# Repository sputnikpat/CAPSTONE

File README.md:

# CAPSTONE
This is the college capstone project.

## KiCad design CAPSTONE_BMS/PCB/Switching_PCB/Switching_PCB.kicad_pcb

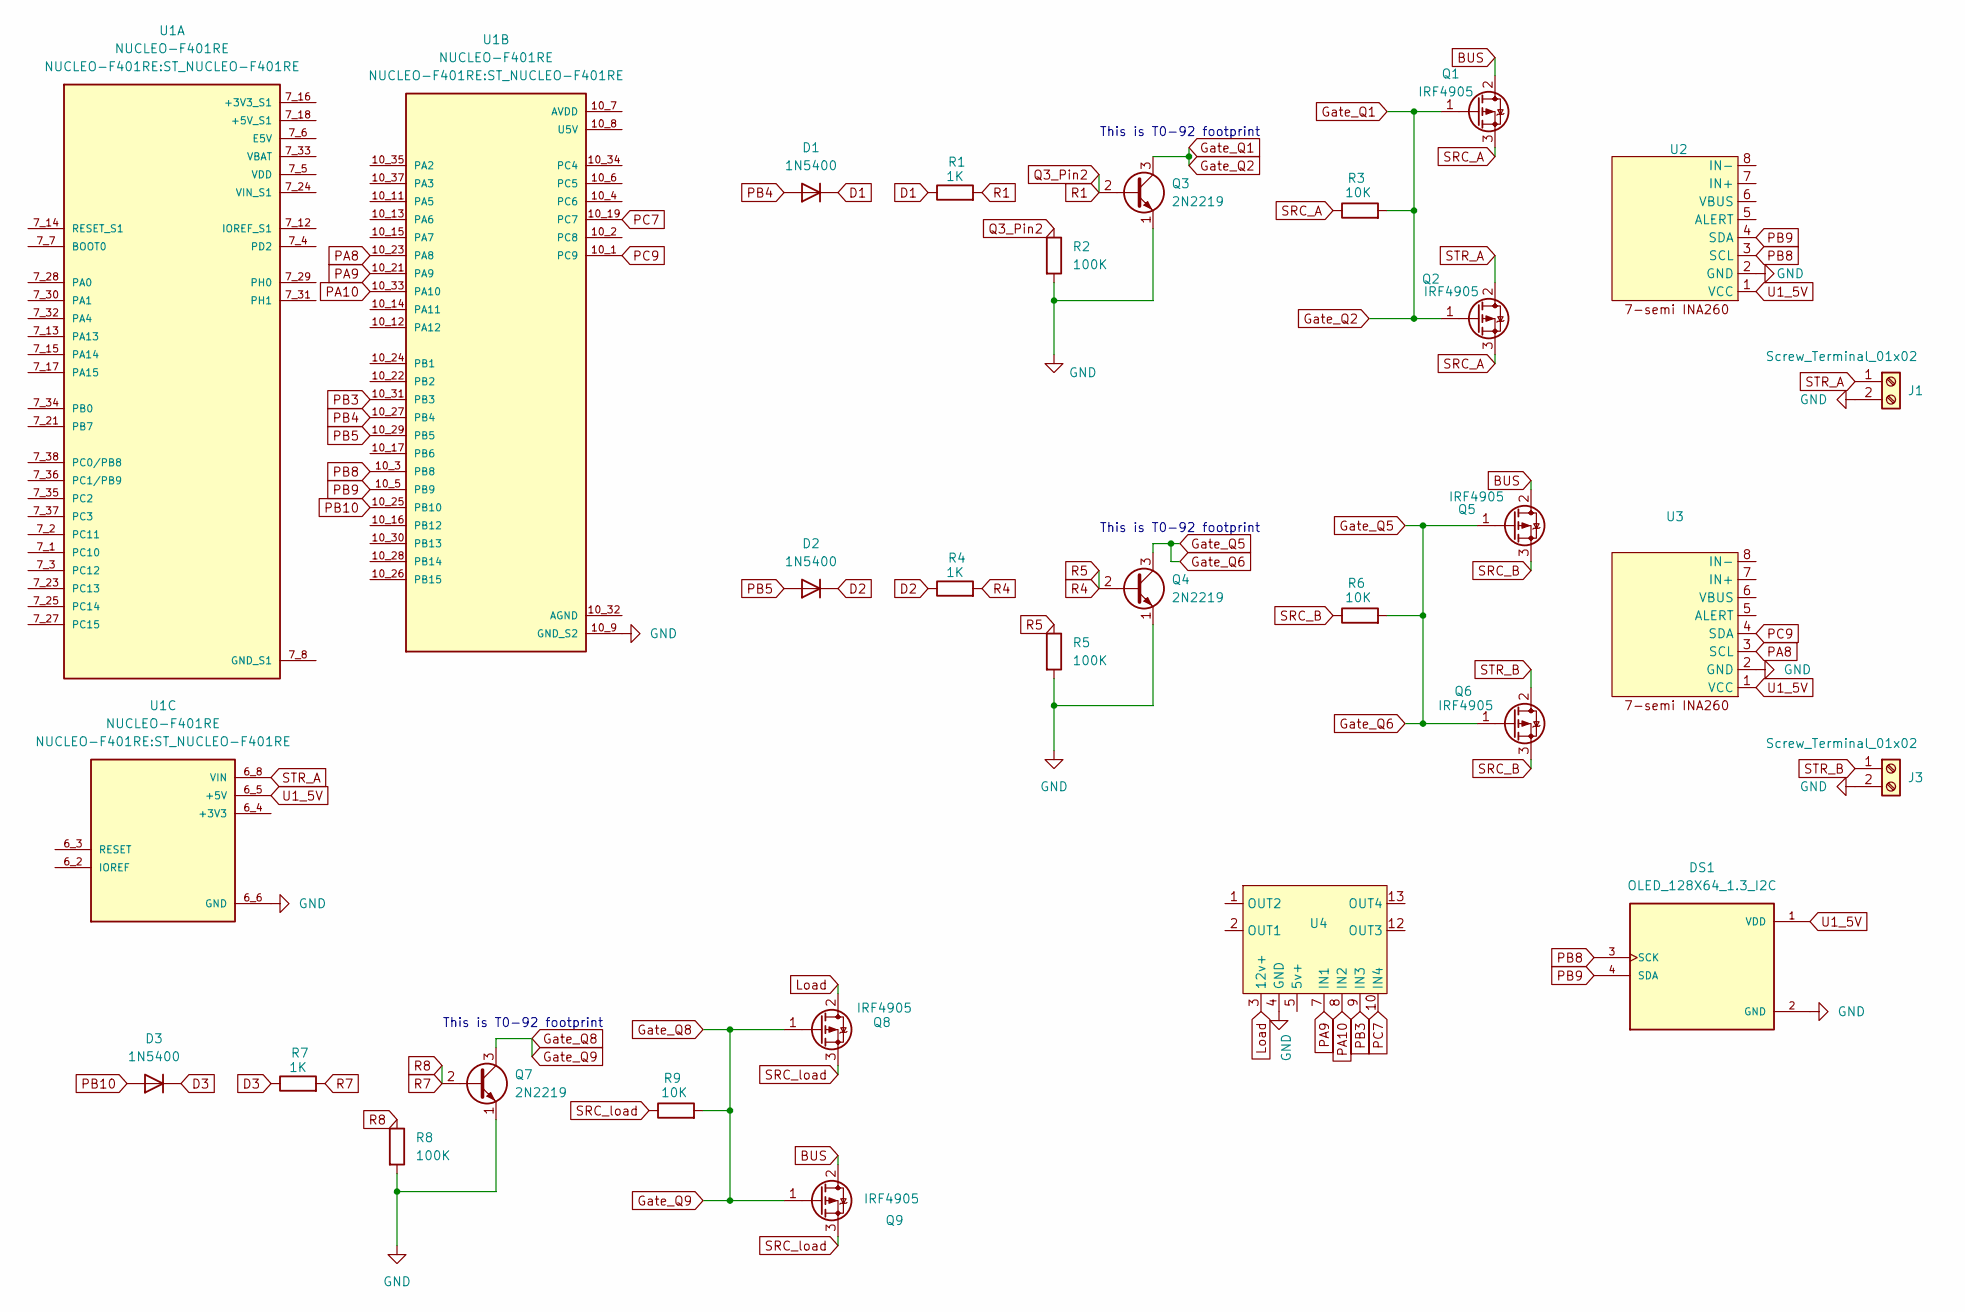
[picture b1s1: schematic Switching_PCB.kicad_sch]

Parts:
D1, D2, D3: 1N5400; D_DO-201AD_P15.24mm_Horizontal
DS1: OLED_128X64_1.3_I2C; LCD_OLED_128X64_1.3_I2C; PARTREV NA
J1, J3: Screw_Terminal_01x02; TerminalBlock_MaiXu_MX126-5.0-02P_1x02_P5.00mm
Q1, Q2, Q5, Q6, Q8, Q9: IRF4905; TO-220-3_Vertical
Q3, Q4, Q7: 2N2219; TO-92
R1, R4, R7: 1K; R_Axial_DIN0204_L3.6mm_D1.6mm_P5.08mm_Horizontal
R2, R5, R8: 100K; R_Axial_DIN0204_L3.6mm_D1.6mm_P5.08mm_Horizontal
R3, R6, R9: 10K; R_Axial_DIN0204_L3.6mm_D1.6mm_P5.08mm_Horizontal
U1: NUCLEO-F401RE; ST_NUCLEO-F401RE; PARTREV 13
U2, U3: INA260_board
U4: L298_MotorDriver

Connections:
BUS: Q1.2 (D), Q5.2 (D), Q9.2 (D)
D1: D1.1 (K), R1.1
D2: D2.1 (K), R4.1
D3: D3.1 (K), R7.1
GND: DS1.2 (GND), J1.2, J3.2, Q3.1 (E), Q4.1 (E), Q7.1 (E), R2.2, R5.2, R8.2, U1.6_6 (GND), U1.6_7 (GND), U1.10_9 (GND_S2), U1.10_20 (GND_S2), U2.2 (GND), U3.2 (GND), U4.4 (GND)
GND_S1: U1.7_8 (GND_S1), U1.7_19 (GND_S1), U1.7_20 (GND_S1), U1.7_22 (GND_S1)
Gate_Q1: Q1.1 (G), Q2.1 (G), Q3.3 (C), R3.2
Gate_Q5: Q4.3 (C), Q5.1 (G), Q6.1 (G), R6.2
Gate_Q8: Q7.3 (C), Q8.1 (G), Q9.1 (G), R9.2
Load: Q8.2 (D), U4.3 (12v+)
PA8: U1.10_23 (PA8), U3.3 (SCL)
PA9: U1.10_21 (PA9), U4.7 (IN1)
PA10: U1.10_33 (PA10), U4.8 (IN2)
PB3: U1.10_31 (PB3), U4.9 (IN3)
PB4: D1.2 (A), U1.10_27 (PB4)
PB5: D2.2 (A), U1.10_29 (PB5)
PB8: DS1.3 (SCK), U1.10_3 (PB8), U2.3 (SCL)
PB9: DS1.4 (SDA), U1.10_5 (PB9), U2.4 (SDA)
PB10: D3.2 (A), U1.10_25 (PB10)
PC7: U1.10_19 (PC7), U4.10 (IN4)
PC9: U1.10_1 (PC9), U3.4 (SDA)
Q3_Pin2: Q3.2 (B), R1.2, R2.1
R4: Q4.2 (B), R4.2, R5.1
R7: Q7.2 (B), R7.2, R8.1
SRC_A: Q1.3 (S), Q2.3 (S), R3.1
SRC_B: Q5.3 (S), Q6.3 (S), R6.1
SRC_load: Q8.3 (S), Q9.3 (S), R9.1
STR_A: J1.1, Q2.2 (D), U1.6_8 (VIN)
STR_B: J3.1, Q6.2 (D)
U1_5V: DS1.1 (VDD), U1.6_5 (+5V), U2.1 (VCC), U3.1 (VCC)

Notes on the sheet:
This is T0-92 footprint

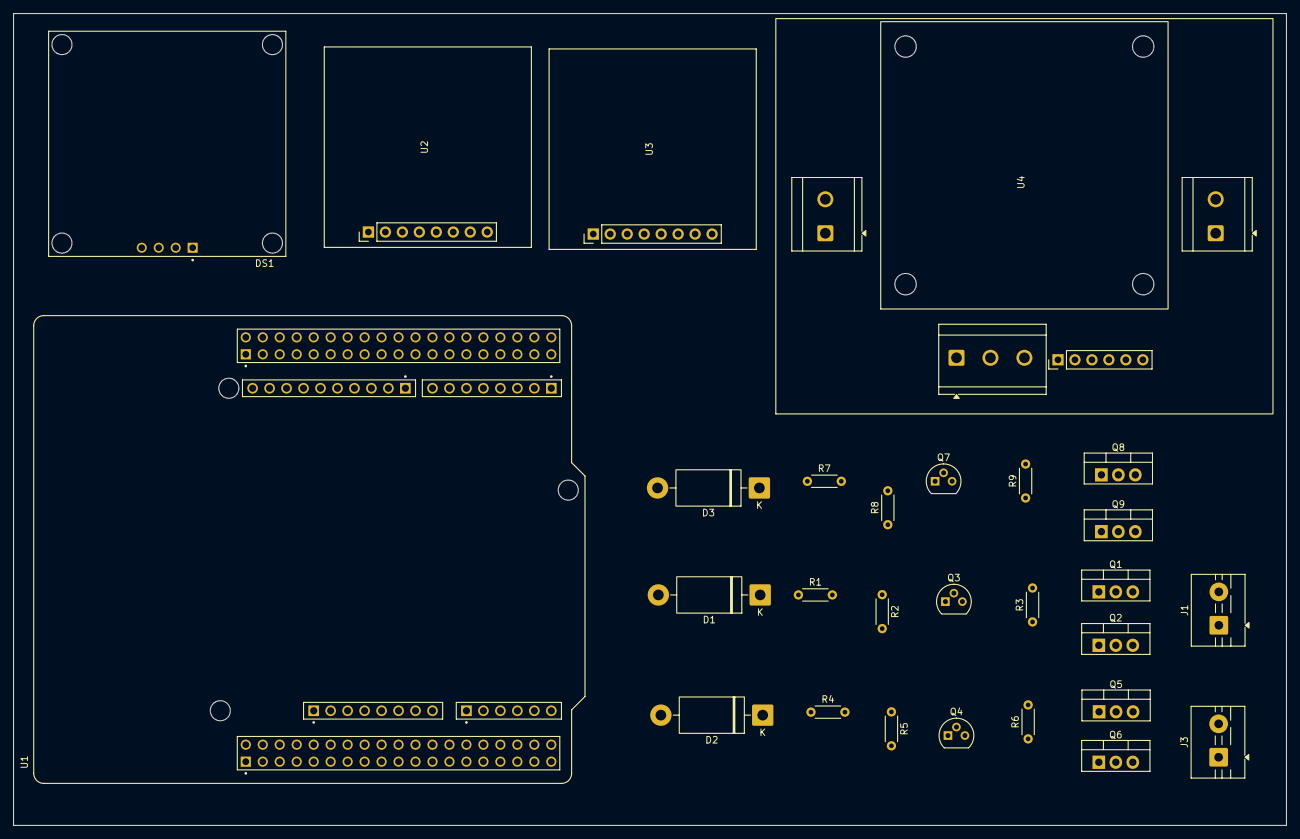
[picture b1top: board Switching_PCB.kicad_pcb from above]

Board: 2 copper layers, 190.5 x 121.5 mm, 28 parts (0 on the bottom side), 30 nets.

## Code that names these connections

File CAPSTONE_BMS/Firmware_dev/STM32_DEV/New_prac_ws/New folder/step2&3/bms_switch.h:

/*
 * bms_switch.h — low-level MOSFET switch control
 *
 *  SCOPE: this module is deliberately DUMB. It knows how to set and clear
 *  individual switches and how to force everything off. It does NOT know
 *  about break-before-make ordering, precharge, dV gating or cooldown —
 *  that sequencing is the project's novel contribution and lives in its
 *  own module (reconfig.c) so it stays separable from generic code.
 *
 *  HARDWARE (from STM32F446RE_Pin_Map_v3.md and the fabricated PCB):
 *    PB4  -> Q3 base -> Gate_Q1  -> Q1/Q2 pair  : String A main
 *    PB5  -> Q4 base -> Gate_Q5  -> Q5/Q6 pair  : String B main
 *    PB10 -> Q7 base -> Gate_Q8  -> Q8/Q9 pair  : Load disconnect
 *
 *  Logic sense: GPIO HIGH -> NPN saturates -> gate pulled to ~0.3 V ->
 *  VGS ~ -10.6 V -> P-channel pair conducts. GPIO LOW -> 10k pull-up
 *  holds gate at source -> VGS = 0 -> pair off, blocking both directions.
 *
 *  >> PRECHARGE IS NOT POPULATED ON THIS BOARD. The milestone plan
 *     specifies a 4th pair (PB6) plus a 10 ohm resistor and bulk cap, but
 *     the fabricated PCB has only three pairs. Any parallel-connect must
 *     therefore satisfy the dV < 0.1 V gate by waiting for natural
 *     settling, NOT by precharging. M0 measured 218.8 A on a cold connect
 *     without precharge — the state machine must never close a second
 *     string onto a live bus with an unverified dV.
 *
 *  >> VERIFY in CubeMX: SYS -> Debug -> Serial Wire. PB4 is NJTRST and
 *     PB3 is JTDO at reset; if debug mode is left at JTAG neither works
 *     as GPIO and String A simply will not switch.
 */

#ifndef BMS_SWITCH_H
#define BMS_SWITCH_H

#include "main.h"

/* ---- Pin definitions ---- */
#define SW_PORT             GPIOB

#define SW_STRING_A_PIN     GPIO_PIN_4
#define SW_STRING_B_PIN     GPIO_PIN_5
#define SW_LOAD_PIN         GPIO_PIN_10

/* All switch pins, for a single atomic all-off write */
#define SW_ALL_PINS         (SW_STRING_A_PIN | SW_STRING_B_PIN | SW_LOAD_PIN)

typedef enum {
    SW_STRING_A = 0,
    SW_STRING_B,
    SW_LOAD,
    SW_COUNT
} SwitchId;

typedef enum {
    SW_OFF = 0,
    SW_ON  = 1
} SwitchState;

/**
 * @brief  Configure all switch GPIOs as outputs and drive them LOW.
 *         MUST be called before anything else that could energise the bus.
 *         Safe to call repeatedly.
 */
void Switch_Init(void);

/**
 * @brief  Set one switch. No sequencing, no interlocks — the caller owns
 *         ordering. Returns 1 if the id was valid.
 */
uint8_t Switch_Set(SwitchId id, SwitchState state);

/**
 * @brief  Read back the commanded state of one switch (what the GPIO
 *         output register says, NOT what the MOSFET is actually doing).
 *         Real state validation needs a current/voltage readback and is
 *         done in the state machine.
 */
SwitchState Switch_Get(SwitchId id);

/**
 * @brief  Force every switch off in a single register write.
 *         Uses direct BSRR access, not HAL, so it still works if HAL
 *         itself is the failed subsystem. Interrupt-safe and atomic.
 *         This is the safe state: all pairs blocking in both directions.
 */
void Switch_AllOff(void);

/**
 * @brief  Human-readable name, for OLED/UART.
 */
const char *Switch_Name(SwitchId id);

#endif /* BMS_SWITCH_H */

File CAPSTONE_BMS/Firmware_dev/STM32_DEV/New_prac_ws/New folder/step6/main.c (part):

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  *    is unaffected (shortest timeout 340 ms).
  *
  *  CUBEMX — REQUIRED (unchanged from Step 5)
  *    - I2C3 on PA8 (SCL) / PC9 (SDA), 100 kHz
  *    - SYS -> Debug -> Serial Wire                     (frees PB4 AND PB3)
  *    - Do NOT enable IWDG in CubeMX (started by hand, see Watchdog_Start).
  ******************************************************************************
  */
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static void I2C1_Reinit(void) { MX_I2C1_Init(); }
static void I2C3_Reinit(void) { MX_I2C3_Init(); }

I2C_Bus bus_i2c1 = { &hi2c1, GPIOB, GPIO_PIN_8, I2C1_Reinit, 0 };  /* SCL PB8 */
I2C_Bus bus_i2c3 = { &hi2c3, GPIOA, GPIO_PIN_8, I2C3_Reinit, 0 };  /* SCL PA8 */

static int32_t Round_mA(float mA)
{
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  HAL_NVIC_EnableIRQ(EXTI15_10_IRQn);

  /* USER CODE BEGIN MX_GPIO_Init_2 */
  /* Switch pins PB4/PB5/PB10 are owned by Switch_Init() (bms_switch.c). */
  /* USER CODE END MX_GPIO_Init_2 */
}

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
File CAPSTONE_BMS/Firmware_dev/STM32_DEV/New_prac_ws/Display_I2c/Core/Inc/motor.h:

/*
 * motor.h
 *
 * L298N motor driver interface for 2-wheel rover
 * Direction control only (ENA/ENB jumpered to 5V on L298N module)
 *
 * Pin assignments (from spare GPIO list in STM32F446RE_GPIO_Pin_Map):
 *   PA9  (D8)  -> L298N IN1  (Motor A direction 1)
 *   PA10 (D2)  -> L298N IN2  (Motor A direction 2)
 *   PC7  (D9)  -> L298N IN3  (Motor B direction 1)
 *   PB3  (D3)  -> L298N IN4  (Motor B direction 2)
 *
 * NOTE: PB3 is also SWO trace pin. Safe as GPIO if SWO is unused.
 *       Verify no conflict in CubeMX.
 *
 * Forward:  IN1=HIGH, IN2=LOW,  IN3=HIGH, IN4=LOW
 * Stop:     IN1=LOW,  IN2=LOW,  IN3=LOW,  IN4=LOW   (coast stop)
 * Brake:    IN1=HIGH, IN2=HIGH, IN3=HIGH, IN4=HIGH   (short brake)
 *
 * IMPORTANT: "Forward" depends on your motor wiring polarity.
 *            If a wheel spins backward, swap IN1/IN2 or IN3/IN4 at
 *            the L298N terminal, or invert the defines below.
 */

#ifndef MOTOR_H
#define MOTOR_H

#include "main.h"

/* ---- Pin definitions ---- */
/* Must match MX_GPIO_Init() configuration in main.c */

#define MOTOR_A_IN1_PIN    GPIO_PIN_9
#define MOTOR_A_IN1_PORT   GPIOA

#define MOTOR_A_IN2_PIN    GPIO_PIN_10
#define MOTOR_A_IN2_PORT   GPIOA

#define MOTOR_B_IN3_PIN    GPIO_PIN_7
#define MOTOR_B_IN3_PORT   GPIOC

#define MOTOR_B_IN4_PIN    GPIO_PIN_3
#define MOTOR_B_IN4_PORT   GPIOB

/* ---- Function prototypes ---- */

void Motor_GPIO_Init(void);   /* Configure IN1-IN4 as push-pull outputs */
void Motor_Forward(void);     /* Both motors forward                    */
void Motor_Stop(void);        /* Both motors coast stop (all LOW)       */
void Motor_Brake(void);       /* Both motors short brake (all HIGH)     */

#endif /* MOTOR_H */
